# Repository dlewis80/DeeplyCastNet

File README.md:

# DeeplyCastNet
Senior Design Project to make an Underwater Acoustic Modem for swarm robotics

Check out our [wiki](https://github.com/dlewis80/DeeplyCastNet/wiki) for more information!

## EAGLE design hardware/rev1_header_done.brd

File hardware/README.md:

# DeeplyCastNet
Contains hardware design source files

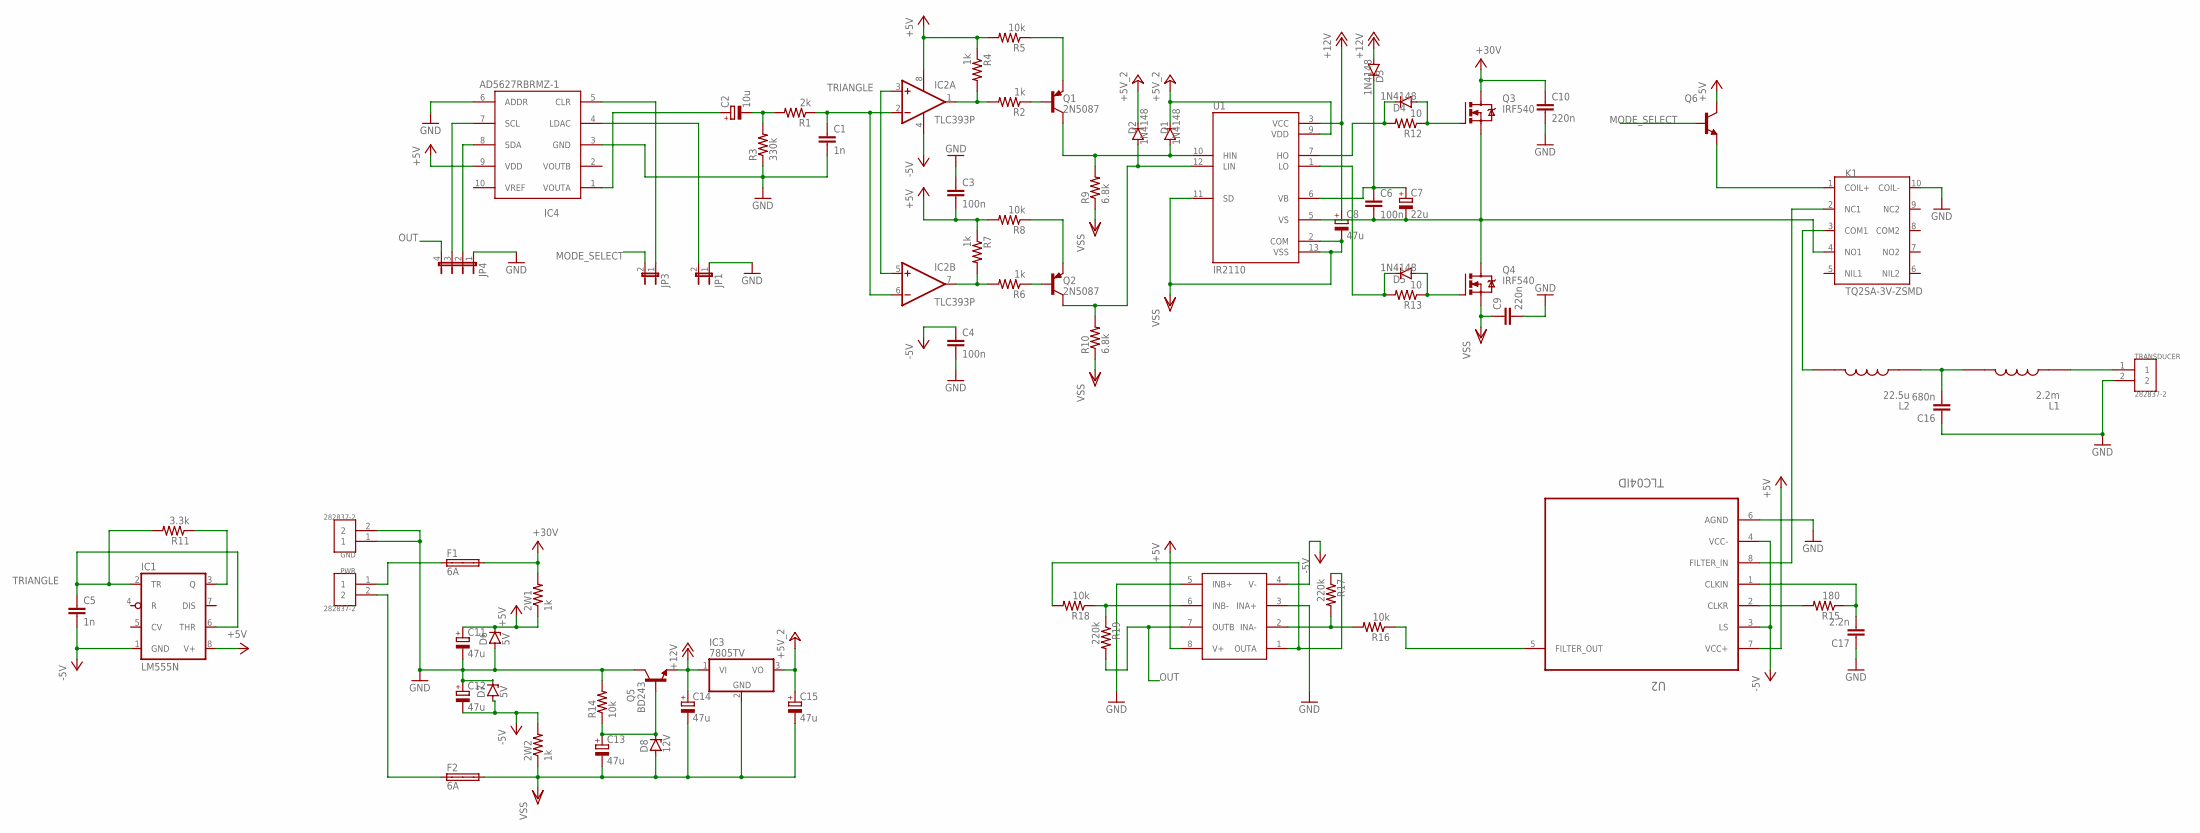
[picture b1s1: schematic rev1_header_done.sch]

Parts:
2W1, 2W2: 1k; V235/17
C1, C5: 1n; C050-025X075
C2: 10u; E2,5-6E
C3, C4, C6: 100n; C050-025X075
C7: 22u; E2,5-6E
C8, C11, C12, C13, C14, C15: 47u; E2,5-6E
C9, C10: 220n; C050-025X075
C16: 680n; C050-025X075
C17: 2.2n; C050-025X075
D1, D2, D3, D4, D5: 1N4148; DO35-7
D6, D7: 5V; DO41Z10
D8: 12V; DO41Z10
F1, F2: 6A; SHK20L
GND: 282837-2; TE_282837-2
IC1: LM555N; DIL08
IC2: TLC393P; DIL08
IC3: 7805TV; TO220V
IC4: AD5627RBRMZ-1; SOP50P490X110-10N
IC5: OP2177CRMZ; SOP65P490X110-8N
JP1, JP3: JP1E; JP1
JP4: JP4E; JP4
K1: TQ2SA-3V-ZSMD; TQ2SA-3V-Z
L1: 2.2m; IND_LQH43NN222K03L
L2: 22.5u; IND_LQH43NN222K03L
PWR: 282837-2; TE_282837-2
Q1, Q2: 2N5087; TO92
Q3, Q4: IRF540; TO220BV
Q5: BD243; TO220
Q6: -NPN-TO92; TO92
R1: 2k; V234/12
R2, R4, R6, R7: 1k; V234/12
R3: 330k; V234/12
R5, R8, R14, R16, R18: 10k; V234/12
R9, R10: 6.8k; V234/12
R11: 3.3k; V234/12
R12, R13: 10; V234/12
R15: 180; V234/12
R17, R19: 220k; V234/12
TRANSDUCER: 282837-2; TE_282837-2
U1: IR2110; DIP762W45P254L2019H533Q14
U2: TLC04ID; SOIC127P600X175-8N

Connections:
+5V: 2W1.1, C3.2, C11.+, D6.C, IC1.8 (V+), IC2.8 (V+), IC4.9 (VDD), IC5.8 (V+), Q6.3 (C), R4.1, R5.2, R7.1, R8.2, U2.7 (VCC+)
+5V_2: C15.+, D1.C, D2.C, IC3.3 (VO), U1.9 (VDD)
+12V: C8.+, C14.+, D3.A, IC3.1 (VI), Q5.3 (E), U1.3 (VCC)
-5V: 2W2.2, C4.1, C5.2, C12.-, D7.A, IC1.1 (GND), IC2.4 (V-), IC5.4 (V-), U2.3 (LS), U2.4 (VCC-)
CLR: IC4.5 (CLR), JP3.1
GND: C1.2, C3.1, C4.2, C9.2, C10.2, C11.-, C12.+, C16.1, C17.1, D6.A, D7.C, GND.1, GND.2, IC4.3 (GND), IC4.6 (ADDR), IC5.3 (INA+), IC5.5 (INB+), JP1.1, JP4.1, K1.10 (COIL-), Q5.2 (C), R3.1, R14.2, TRANSDUCER.2, U2.6 (AGND)
H_GATE: D4.A, Q3.G, R12.1
LDAC: IC4.4 (LDAC), JP1.2
L_GATE: D5.A, Q4.G, R13.1
MODE_SELECT: JP3.2, Q6.2 (B)
unnamed: C2.+, IC4.1 (VOUTA)
unnamed: C2.-, R1.2, R3.2
unnamed: C1.1, IC2.2 (-IN), IC2.6 (-IN), R1.1
unnamed: IC2.1 (OUT), R2.2, R4.2
unnamed: Q1.2 (B), R2.1
unnamed: Q1.3 (E), R5.1
unnamed: IC2.7 (OUT), R6.2, R7.2
unnamed: Q2.3 (E), R8.1
unnamed: Q2.2 (B), R6.1
unnamed: D1.A, Q1.1 (C), R9.2, U1.10 (HIN)
unnamed: D2.A, Q2.1 (C), R10.2, U1.12 (LIN)
unnamed: IC1.3 (Q), R11.1
unnamed: C6.1, C7.+, D3.C, U1.6 (VB)
unnamed: C16.2, L1.2, L2.1
unnamed: D4.C, R12.2, U1.7 (HO)
unnamed: D5.C, R13.2, U1.1 (LO)
unnamed: K1.3 (COM1), L2.2
unnamed: K1.1 (COIL+), Q6.1 (E)
unnamed: L1.1, TRANSDUCER.1
unnamed: F1.1A, PWR.1
unnamed: F2.1A, PWR.2
unnamed: C13.+, D8.C, Q5.1 (B), R14.1
unnamed: K1.2 (NC1), U2.8 (FILTER_IN)
unnamed: R15.2, U2.2 (CLKR)
unnamed: C17.2, R15.1, U2.1 (CLKIN)
unnamed: R16.1, U2.5 (FILTER_OUT)
unnamed: IC5.2 (INA-), R16.2, R17.2
unnamed: IC5.1 (OUTA), R17.1, R18.2
unnamed: IC5.6 (INB-), R18.1, R19.1
OUT: IC5.7 (OUTB), JP4.4, R19.2
SCL: IC4.7 (SCL), JP4.3
SDA: IC4.8 (SDA), JP4.2
TRANSMIT: C6.2, C7.-, K1.4 (NO1), Q3.S, Q4.D, U1.5 (VS)
TRIANGLE: C5.1, IC1.2 (TR), IC1.6 (THR), IC2.3 (+IN), IC2.5 (+IN), R11.2
V+: 2W1.2, C10.1, F1.2A, Q3.D
VSS: 2W2.1, C8.-, C9.1, C13.-, C14.-, C15.-, D8.A, F2.2A, IC3.2 (GND), Q4.S, R9.1, R10.1, U1.2 (COM), U1.11 (SD), U1.13 (VSS)

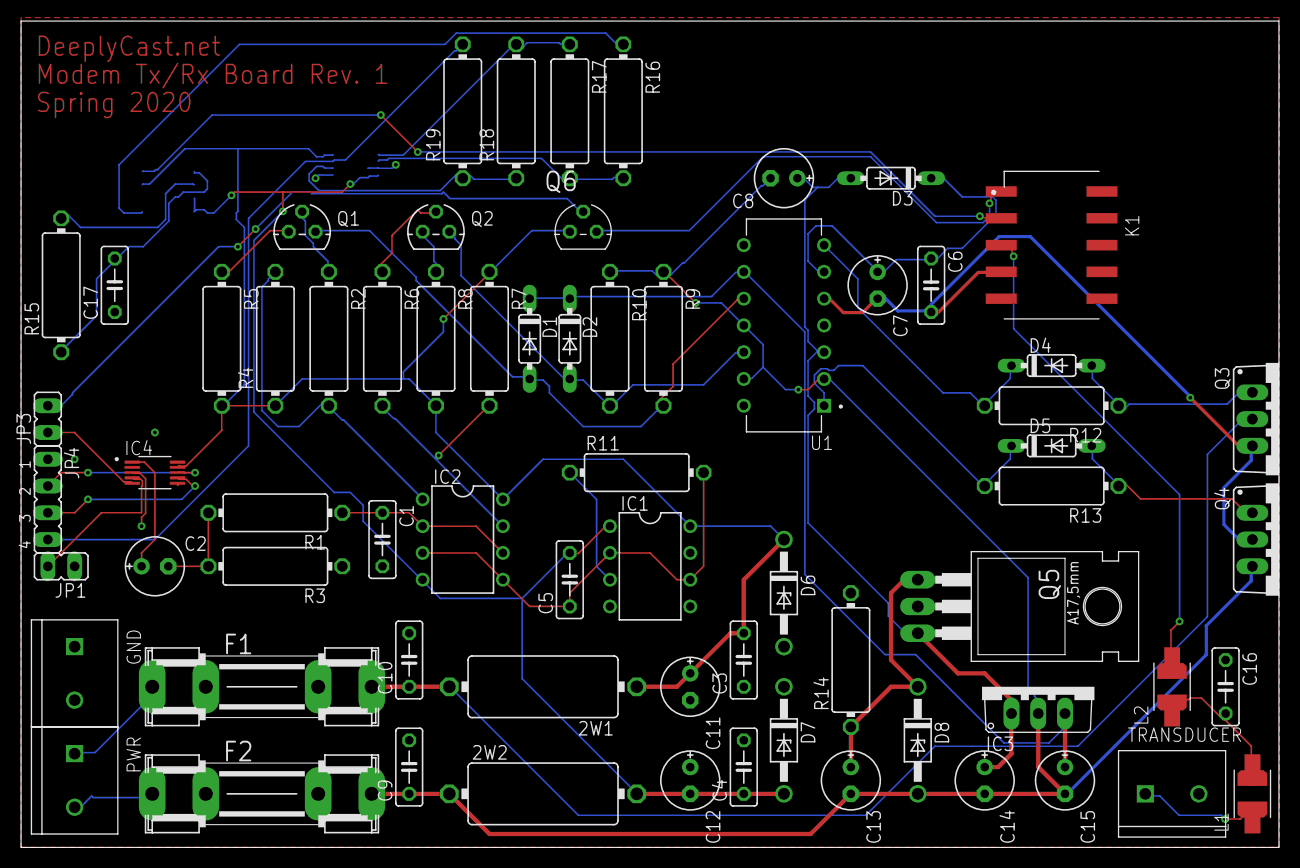
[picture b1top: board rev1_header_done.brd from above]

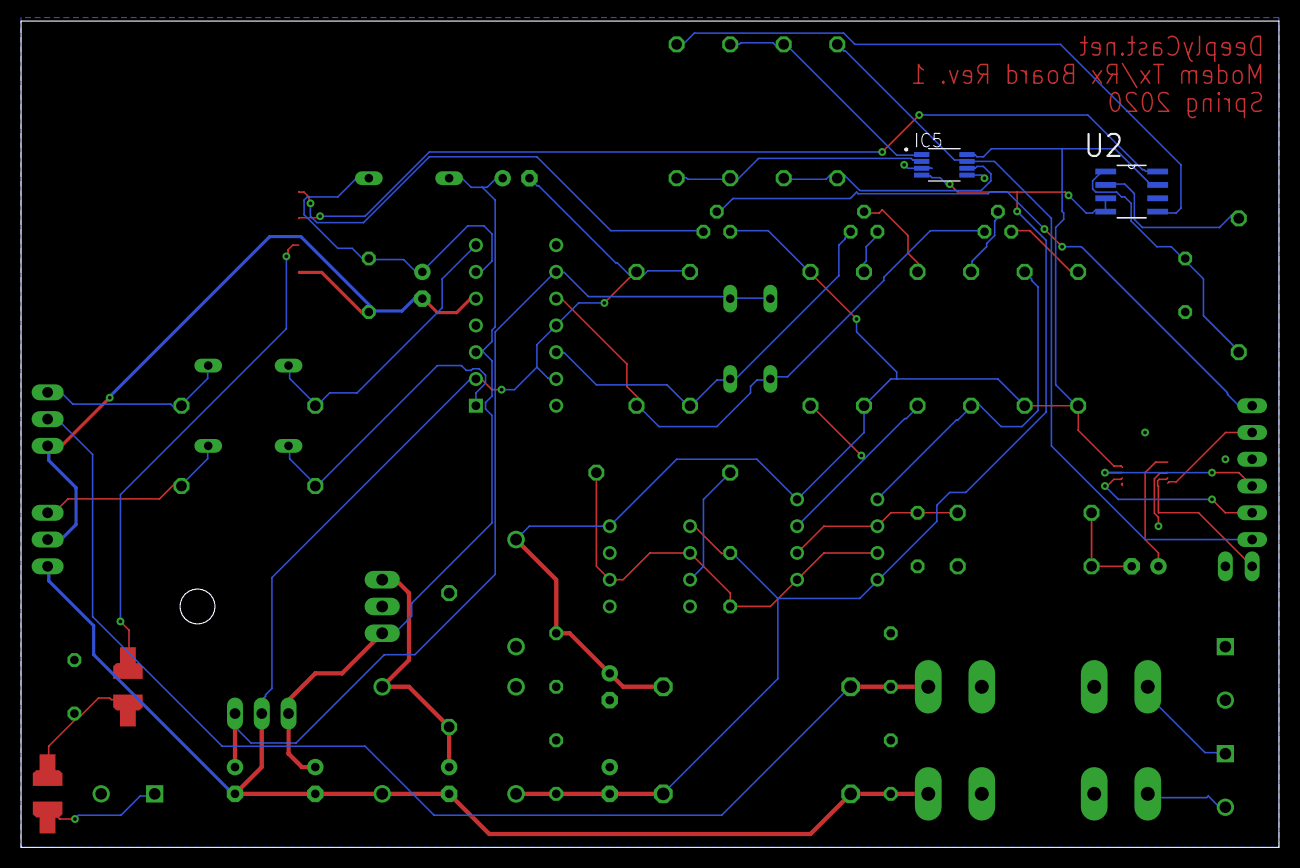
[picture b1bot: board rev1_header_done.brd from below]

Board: 2 copper layers, 119.4 x 78.4 mm, 70 parts (2 on the bottom side), 46 nets.

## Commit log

2020-02-24 Initialize Directory Structure
2020-02-24 Added goertzel_profiler matlab function
2020-03-05 base code with verfied 100 khz sampling
2020-03-14 Removed old Project
2020-03-14 New project with 100 Khz sampling
2020-04-09 VMATE Initialize. Modem only, no propagation.
2020-04-10 Initial Commit for PC Software
2020-04-26 Update pc app with correct settings options and message structure
2020-04-26 Fixed typo with sendingSettings bool
2020-04-26 very messy prototype with transmit and receive
2020-04-26 Updated pcApp to work with firmwarey
2020-04-27 new transmit architecture
2020-04-27 Added propagation model, rewrote transmitter to accomodate. Needs serious cleaning
2020-04-27 new relay gpio
2020-04-28 Added analog models
2020-04-28 VMATE fully functional. Still needs cleaning
2020-04-28 Reorganization phase 1
2020-04-28 Phase 2 Reorganization
2020-04-28 Phase 3 Reorganization
2020-04-29 Phase 4 Reorganization
2020-04-29 VMATE Cleanup complete, readme added
2020-04-30 Add link to wiki
2020-04-30 Uploaded EAGLE Files
